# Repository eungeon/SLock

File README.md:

# SLock
<center></center><br/>

광주소프트웨어마이스터고등학교 기숙사 출입문 자동화 솔루션을 개발하는 저장소입니다.   

***
## 1. 시작하면서...
### 1.1. 개요
이 프로젝트는 광주소프트웨어마이스터고등학교에서 열리는 2019 GSM Festival에서 출품한 작품이며, 처음에는 프로토타입으로 제작하였다. 처음 프로토 타입은 회로구성을 만능기판에 납땝으로 제작하였으며, Autodesk사의 Fusion 360으로 하우징을 설계, 3D 프린터로 출력, 제작하였다.   
GSM Festival이 끝난 후, 좀 더 하드웨어를 높은 퀄리티로 만들어 보고자 PCB를 설계, 제작하여 좀더 소형화 시켜서 제작 후 본교 기숙사에 설치를 목표로 제작 할 예정이다.

### 1.2. Workflow
> GSM Festival을 진행하면서 제작한 흐름도이며, 업데이트가 필요하다.
> #### 1.2.1 System WorkFlow
> 
> #### 1.2.2 Hardware WorkFlow
> 
> 
   
***
## 2. PCB Work
PCB 설계는 Autodesk사의 Eagle CAD를 사용하였으며, 아직 초보이기에 개선해야 할 부분이 많다.
### 2.1. Library
PCB 설계에 필요한 추가적인 User Library 를 사용하였으며, 본 저장소에 업로드되어 있다.
```
SLock\SLock_Circuit\libraries
```

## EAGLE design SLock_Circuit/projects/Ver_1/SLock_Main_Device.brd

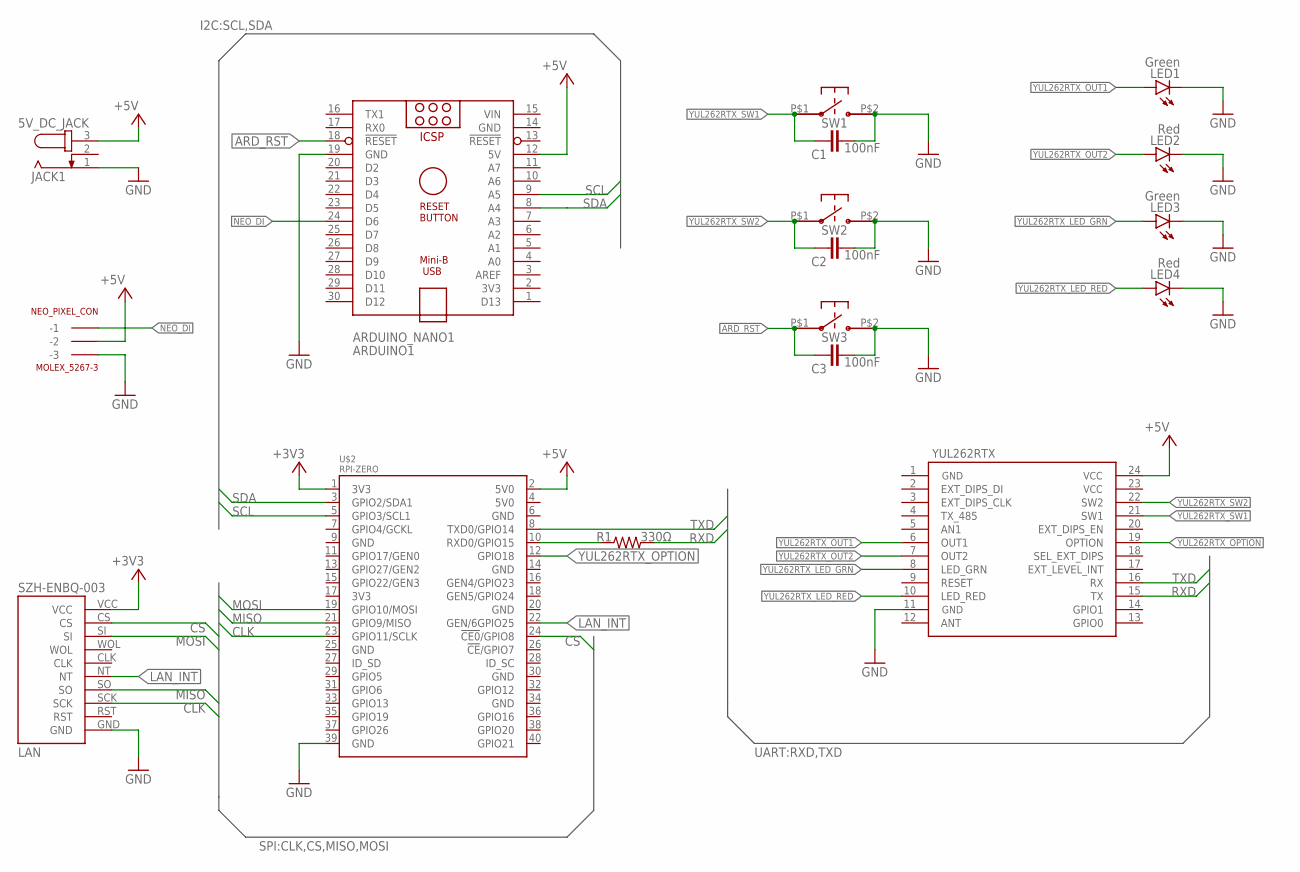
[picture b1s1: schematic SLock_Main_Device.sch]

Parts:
5V_DC_JACK: JACK1; SPC4077
ARDUINO_NANO1: ARDUINO1; ARDUINO_NANO
C1, C2, C3: 100nF; C050-024X044
LAN: SZH-ENBQ-003
LED1, LED3: Green; LED3MM
LED2, LED4: Red; LED3MM
NEO_PIXEL_CON: MOLEX_5267-3; 5267-3
R1: 330Ω; 0204/7
SW1, SW2, SW3: SKPDAMD010
U$2: RPI-ZERO; RASPBERRYPI_BASTELSTUBE_V13_RASPI_BOARD_B+_FULL
YUL262RTX: YUL262RTX; YUL262RXT_HOLE

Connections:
+3V3: LAN.VCC, U$2.1 (3V3)
+5V: 5V_DC_JACK.3, ARDUINO_NANO1.12 (5V), NEO_PIXEL_CON.P$2 (-2), U$2.2 (5V0), YUL262RTX.24 (VCC_2)
ARD_RST: ARDUINO_NANO1.18 (!RESET), C3.1, SW3.P$1
CLK: LAN.SCK, U$2.23 (GPIO11/SCLK)
CS: LAN.CS, U$2.24 (!CE0!/GPIO8)
GND: 5V_DC_JACK.1, ARDUINO_NANO1.14 (GND), ARDUINO_NANO1.19 (GND), C1.2, C2.2, C3.2, LAN.GND, LED1.K (C), LED2.K (C), LED3.K (C), LED4.K (C), NEO_PIXEL_CON.P$3 (-3), SW1.P$2, SW2.P$2, SW3.P$2, U$2.39 (GND), YUL262RTX.11 (GND_1)
GND_2: YUL262RTX.1 (GND_2)
LAN_INT: LAN.NT, U$2.22 (GEN/6GPIO25)
MISO: LAN.SO, U$2.21 (GPIO9/MISO)
MOSI: LAN.SI, U$2.19 (GPIO10/MOSI)
NEO_DI: ARDUINO_NANO1.24 (D6), NEO_PIXEL_CON.P$1 (-1)
RXD: R1.2, YUL262RTX.15 (TX)
RXD_INPUT: R1.1, U$2.10 (RXD0/GPIO15)
SCL: ARDUINO_NANO1.9 (A5), U$2.5 (GPIO3/SCL1)
SDA: ARDUINO_NANO1.8 (A4), U$2.3 (GPIO2/SDA1)
TXD: U$2.8 (TXD0/GPIO14), YUL262RTX.16 (RX)
VCC_1: YUL262RTX.23 (VCC_1)
VIN: ARDUINO_NANO1.15 (VIN)
YUL262RTX_LED_GRN: LED3.A, YUL262RTX.8 (LED_GRN)
YUL262RTX_LED_RED: LED4.A, YUL262RTX.10 (LED_RED)
YUL262RTX_OPTION: U$2.12 (GPIO18), YUL262RTX.19 (OPTION)
YUL262RTX_OUT1: LED1.A, YUL262RTX.6 (OUT1)
YUL262RTX_OUT2: LED2.A, YUL262RTX.7 (OUT2)
YUL262RTX_SW1: C1.1, SW1.P$1, YUL262RTX.21 (SW1)
YUL262RTX_SW2: C2.1, SW2.P$1, YUL262RTX.22 (SW2)

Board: 2 copper layers, 17 parts (0 on the bottom side), 22 nets, no tracks yet.

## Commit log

2020-01-24 [Added] circuit file
    전에 했던 파일 커밋
2020-01-24 [Changed] Folder structure
    이글캐드 프로젝트 폴더 정리화 및 프로젝트 연결
2020-01-26 [Updated] Main_Device circuit
    위치변경 및 보드 임시 Export
2020-01-26 [Added] Main_device circuit Render image
    임시 Export 한 pcb로 가조립
2020-01-27 [Added] YUL262RTX 3D file
    라디오리써치社의 YUL262RTX RF 모듈을 3D file 로 제작
    각각 step file, fbx file로 Export.
2020-01-27 [Added] old work flow image
    전에 제작한 워크플로우 및 로고 업로드.
    교체 예정.
2020-01-27 [Changed] flow image rename
    이미지 이름을 좀더 간결하게 수정
2020-01-27 Update README.md
    PCB 부분 설명 추가
2020-01-29 [Updated] gitignore
    맥에서 생성되는 .DS_Store 파일을 gitignore에 추가. 아직 해도 되는지 알 수 없지만 추가함. 확인 필요
2020-10-21 [Added] gateway src
2020-10-21 [Added] gateway LED control src
2020-10-21 [Added] node_device src
2020-10-21 [Moved] developing src int dev dir
